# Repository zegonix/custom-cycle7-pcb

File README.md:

This repository holds the design sources for a custom PCB and plate for the cycle 7 by TKD. I ordered a prototype and got that working but I do not guarantee anything.

***Note that I used a 12 MHz oscillator instead of an 8 MHz which would be QMKs default frequency for the STM32F401. That is no problem, but requires a little extra configuration. If you don't fancy that, change the oscillator circuit to 8 MHz.***

***Also the design replaces the standard 6.25u spacebar with a 1.25u key, a 2.75u key and a 2.25u key (in this order from the left). Very few keycap sets come with a 1.25 spacebar key, so you might want to change the design to use a different spacebar configuration. If you do that you also need to adjust the plate. If you plan to use the original plate of the cycle 7 you need to change the pcb design to a default 6.25u spacebar.***

Why make my own pcb for the cycle 7? Bootloader on TKD's PCB ~~is shit~~ does not comply with my requirements. Also the firmware is proprietary.

What about this PCB? Sources are here and free to use however you want. **However use at your own risk, I do not guarantee any of this to be functional**
The QMK configuration for the keyboard is available at [zegonix/zegonix-qmk-configs/zegonix/cycle7](https://github.com/zegonix/zegonix-qmk-configs). Follow the steps described in the readme file to link the folder into your local qmk repository and build the firmware.

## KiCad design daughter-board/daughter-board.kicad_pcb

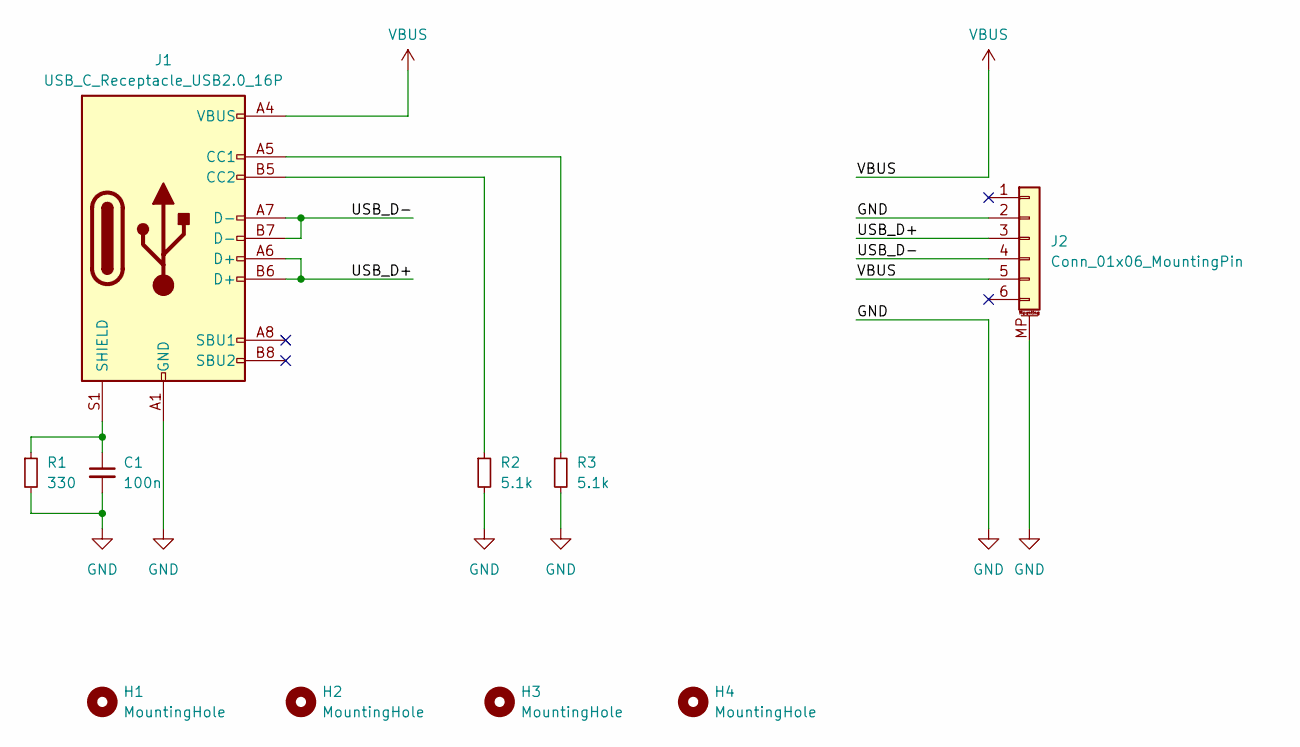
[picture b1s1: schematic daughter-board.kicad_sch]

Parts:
C1: 100n; C_0603_1608Metric
H1, H2, H3, H4: MountingHole; MountingHole_2.2mm_M2
J1: USB_C_Receptacle_USB2.0_16P; USB_C_Receptacle_HRO_TYPE-C-31-M-12
J2: Conn_01x06_MountingPin; JST_SH_SM06B-SRSS-TB_1x06-1MP_P1.00mm_Horizontal
R1: 330; R_0603_1608Metric
R2, R3: 5.1k; R_0603_1608Metric

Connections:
/USB_D+: J1.A6 (D+), J1.B6 (D+), J2.3
/USB_D-: J1.A7 (D-), J1.B7 (D-), J2.4
GND: C1.2, J1.A1 (GND), J1.A12 (GND), J1.B1 (GND), J1.B12 (GND), J2.2, J2.MP (MountPin), R1.2, R2.2, R3.2
unnamed: J1.A5 (CC1), R3.1
unnamed: J1.B5 (CC2), R2.1
unnamed: C1.1, J1.S1 (SHIELD), R1.1
VBUS: J1.A4 (VBUS), J1.A9 (VBUS), J1.B4 (VBUS), J1.B9 (VBUS), J2.5

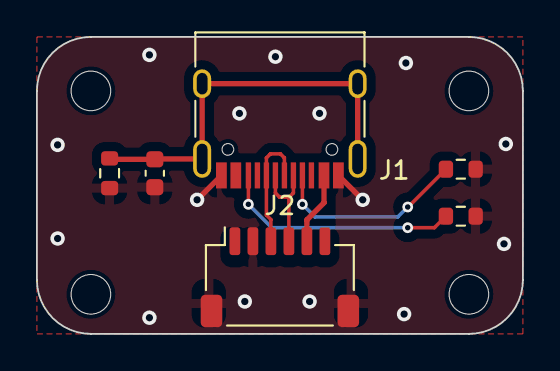
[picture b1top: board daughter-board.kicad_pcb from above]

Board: 2 copper layers, 27.0 x 16.5 mm, 10 parts (0 on the bottom side), 7 nets.

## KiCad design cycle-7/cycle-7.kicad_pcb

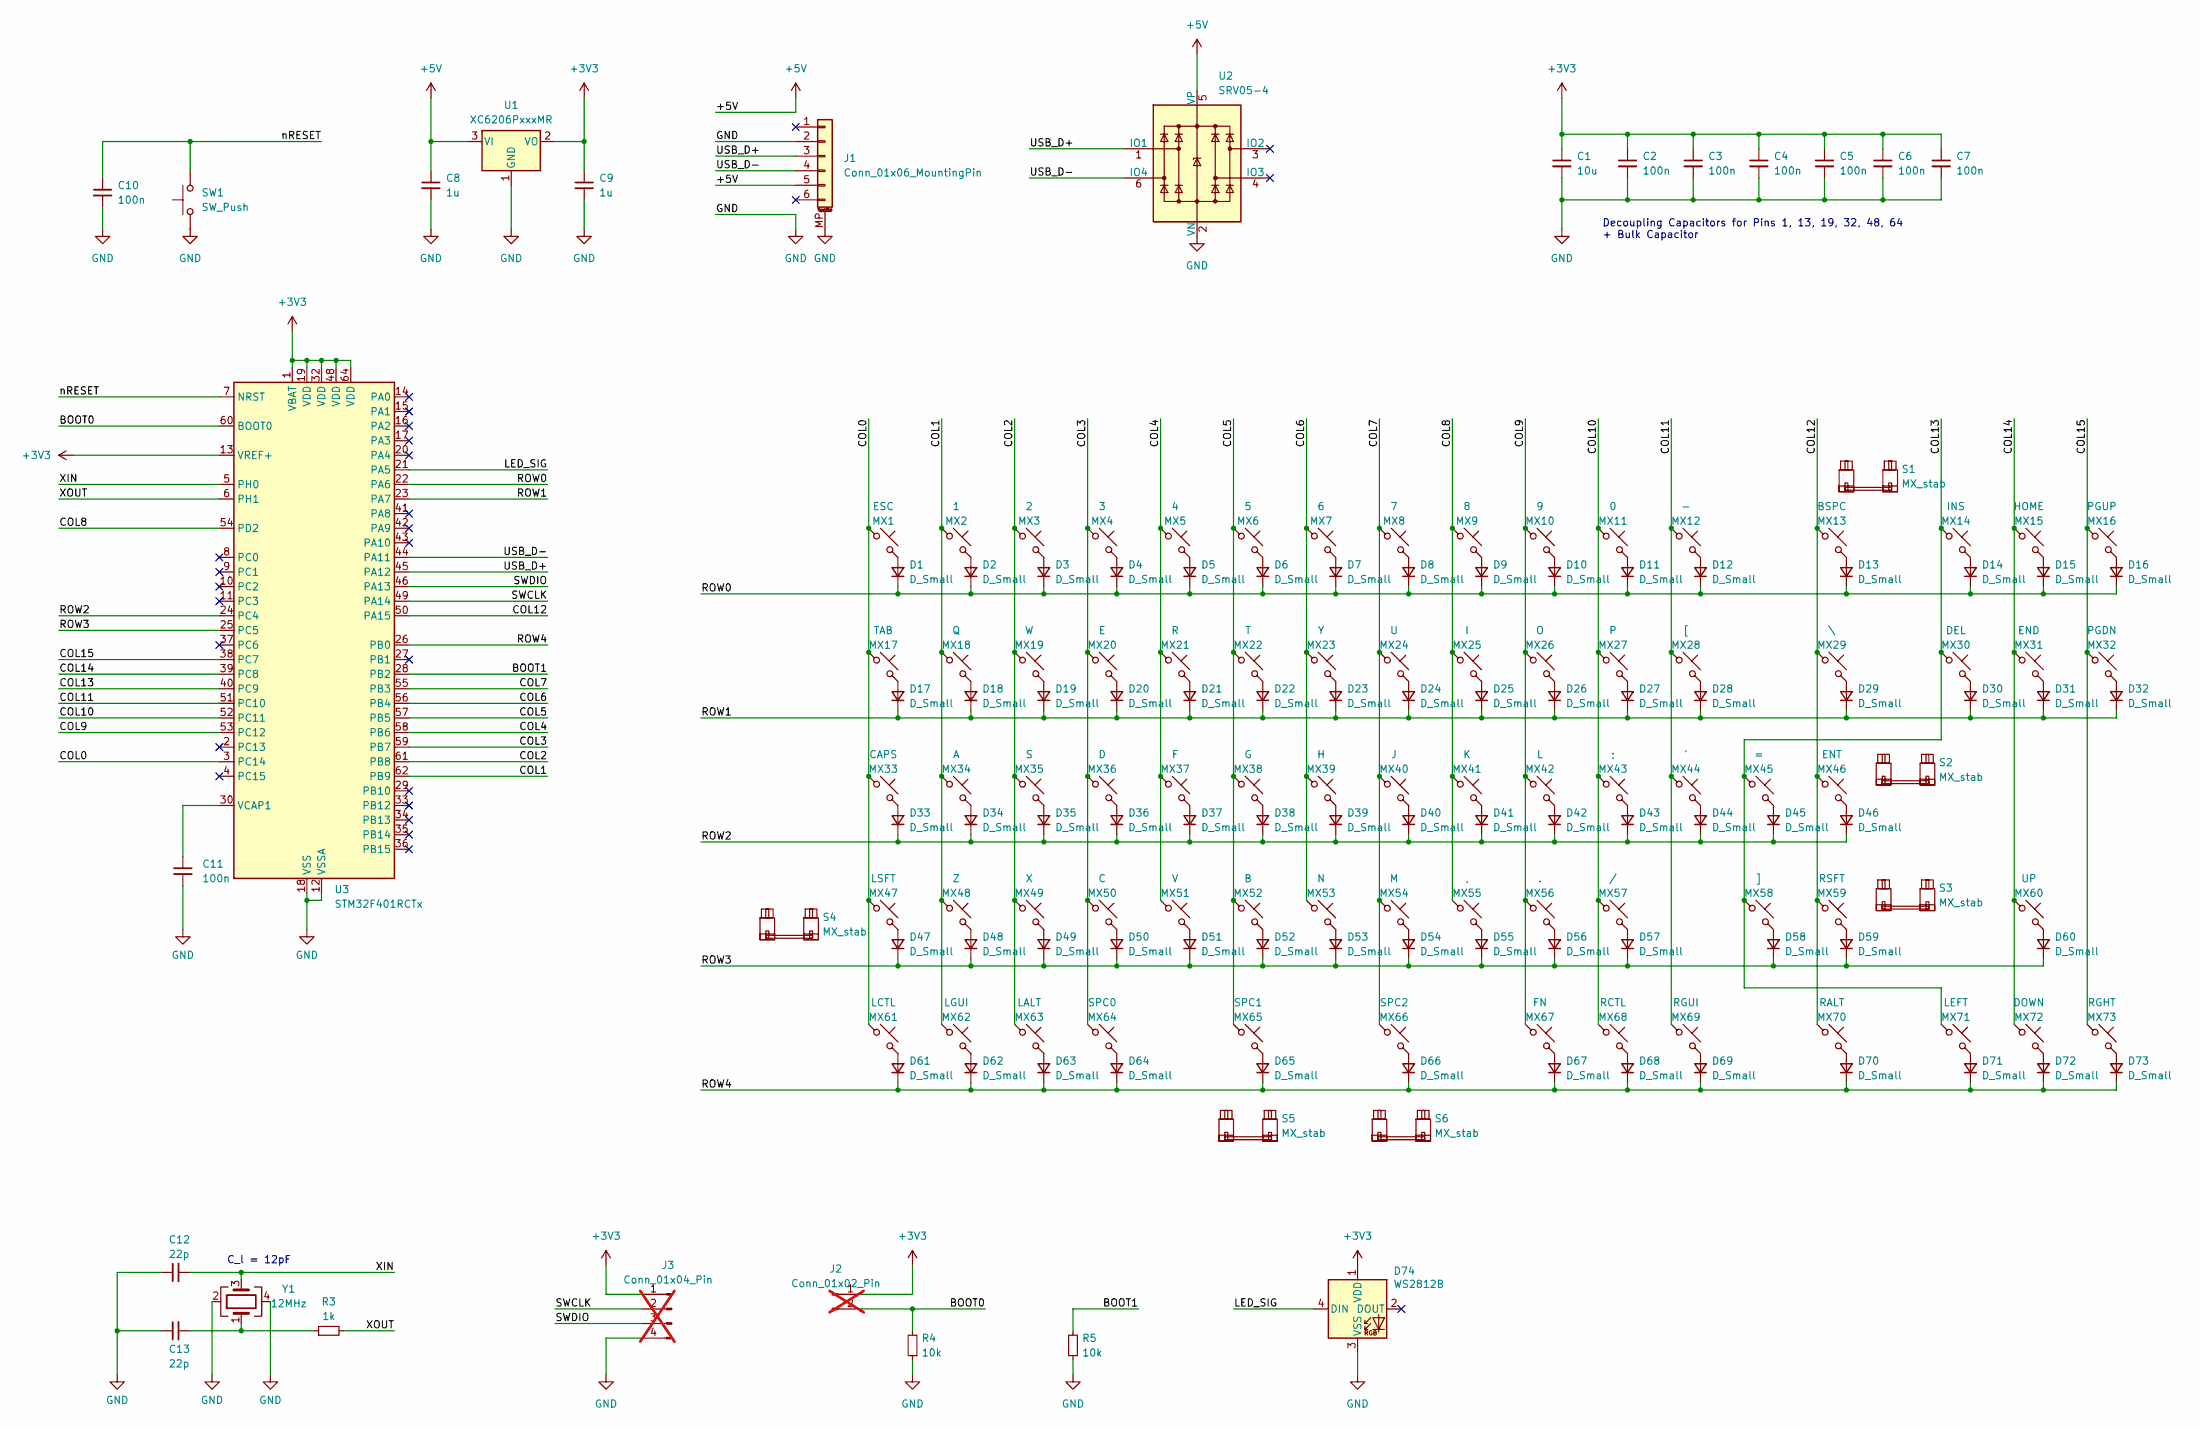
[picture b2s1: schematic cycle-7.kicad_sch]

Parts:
C1: 10u; C_0603_1608Metric
C2, C3, C4, C5, C6, C7, C10, C11: 100n; C_0603_1608Metric
C8, C9: 1u; C_0603_1608Metric
C12, C13: 22p; C_0603_1608Metric
D1, D2, D3, D4, D5, D6, D7, D8, D9, D10, D11, D12, D13, D14, D15, D16, D17, D18, D19, D20, D21, D22, D23, D24, D25, D26, D27, D28, D29, D30, D31, D32, D33, D34, D35, D36, D37, D38, D39, D40, D41, D42, D43, D44, D45, D46, D47, D48, D49, D50, D51, D52, D53, D54, D55, D56, D57, D58, D59, D60, D61, D62, D63, D64, D65, D66, D67, D68, D69, D70, D71, D72, D73: D_Small; D_SOD-123
D74: WS2812B; SK6812MINI-E_3.2x2.8_reverse_mount
J1: Conn_01x06_MountingPin; JST_SH_SM06B-SRSS-TB_1x06-1MP_P1.00mm_Horizontal
J2: Conn_01x02_Pin; PinHeader_1x02_P2.54mm_Vertical; not fitted
J3: Conn_01x04_Pin; PinHeader_1x04_P2.54mm_Vertical; not fitted
MX1, MX2, MX3, MX4, MX5, MX6, MX7, MX8, MX9, MX10, MX11, MX12, MX13, MX14, MX15, MX16, MX18, MX19, MX20, MX21, MX22, MX23, MX24, MX25, MX26, MX27, MX28, MX30, MX31, MX32, MX34, MX35, MX36, MX37, MX38, MX39, MX40, MX41, MX42, MX43, MX44, MX45, MX46, MX47, MX48, MX49, MX50, MX51, MX52, MX53, MX54, MX55, MX56, MX57, MX58, MX59, MX60, MX65, MX66, MX71, MX72, MX73: MX_SW_HS; SW_MX_HS_1u
MX17, MX29: MX_SW_HS; SW_MX_HS_1.5u
MX33: MX_SW_HS; SW_MX_HS_1.75u
MX61, MX62, MX63, MX64, MX67, MX68, MX69, MX70: MX_SW_HS; SW_MX_HS_1.25u
R3: 1k; R_0603_1608Metric
R4, R5: 10k; R_0603_1608Metric
S1: MX_stab; STAB_MX_P_2u
S2, S4, S6: MX_stab; STAB_MX_P_2.25u
S3, S5: MX_stab; STAB_MX_P_2.75u
SW1: SW_Push; SW_SPST_TL3342
U1: XC6206PxxxMR; SOT-23-3
U2: SRV05-4; SOT-23-6-routable
U3: STM32F401RCTx; LQFP-64_10x10mm_P0.5mm
Y1: 12MHz; Crystal_SMD_3225-4Pin_3.2x2.5mm

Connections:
+3V3: C1.1, C2.1, C3.1, C4.1, C5.1, C6.1, C7.1, C9.1, D74.1 (VDD), J2.1, J3.1, U1.2 (VO), U3.1 (VBAT), U3.13 (VREF+), U3.19 (VDD), U3.32 (VDD), U3.48 (VDD), U3.64 (VDD)
+5V: C8.1, J1.5, U1.3 (VI), U2.5 (VP)
/BOOT0: J2.2, R4.2, U3.60 (BOOT0)
/BOOT1: R5.2, U3.28 (PB2)
/COL0: MX1.1, MX17.1, MX33.1, MX47.1, MX61.1, U3.3 (PC14)
/COL1: MX2.1, MX18.1, MX34.1, MX48.1, MX62.1, U3.62 (PB9)
/COL2: MX3.1, MX19.1, MX35.1, MX49.1, MX63.1, U3.61 (PB8)
/COL3: MX4.1, MX20.1, MX36.1, MX50.1, MX64.1, U3.59 (PB7)
/COL4: MX5.1, MX21.1, MX37.1, MX51.1, U3.58 (PB6)
/COL5: MX6.1, MX22.1, MX38.1, MX52.1, MX65.1, U3.57 (PB5)
/COL6: MX7.1, MX23.1, MX39.1, MX53.1, U3.56 (PB4)
/COL7: MX8.1, MX24.1, MX40.1, MX54.1, MX66.1, U3.55 (PB3)
/COL8: MX9.1, MX25.1, MX41.1, MX55.1, U3.54 (PD2)
/COL9: MX10.1, MX26.1, MX42.1, MX56.1, MX67.1, U3.53 (PC12)
/COL10: MX11.1, MX27.1, MX43.1, MX57.1, MX68.1, U3.52 (PC11)
/COL11: MX12.1, MX28.1, MX44.1, MX69.1, U3.51 (PC10)
/COL12: MX13.1, MX29.1, MX46.1, MX59.1, MX70.1, U3.50 (PA15)
/COL13: MX14.1, MX30.1, MX45.1, MX58.1, MX71.1, U3.40 (PC9)
/COL14: MX15.1, MX31.1, MX60.1, MX72.1, U3.39 (PC8)
/COL15: MX16.1, MX32.1, MX73.1, U3.38 (PC7)
/LED_SIG: D74.4 (DIN), U3.21 (PA5)
/ROW0: D1.1 (K), D2.1 (K), D3.1 (K), D4.1 (K), D5.1 (K), D6.1 (K), D7.1 (K), D8.1 (K), D9.1 (K), D10.1 (K), D11.1 (K), D12.1 (K), D13.1 (K), D14.1 (K), D15.1 (K), D16.1 (K), U3.22 (PA6)
/ROW1: D17.1 (K), D18.1 (K), D19.1 (K), D20.1 (K), D21.1 (K), D22.1 (K), D23.1 (K), D24.1 (K), D25.1 (K), D26.1 (K), D27.1 (K), D28.1 (K), D29.1 (K), D30.1 (K), D31.1 (K), D32.1 (K), U3.23 (PA7)
/ROW2: D33.1 (K), D34.1 (K), D35.1 (K), D36.1 (K), D37.1 (K), D38.1 (K), D39.1 (K), D40.1 (K), D41.1 (K), D42.1 (K), D43.1 (K), D44.1 (K), D45.1 (K), D46.1 (K), U3.24 (PC4)
/ROW3: D47.1 (K), D48.1 (K), D49.1 (K), D50.1 (K), D51.1 (K), D52.1 (K), D53.1 (K), D54.1 (K), D55.1 (K), D56.1 (K), D57.1 (K), D58.1 (K), D59.1 (K), D60.1 (K), U3.25 (PC5)
/ROW4: D61.1 (K), D62.1 (K), D63.1 (K), D64.1 (K), D65.1 (K), D66.1 (K), D67.1 (K), D68.1 (K), D69.1 (K), D70.1 (K), D71.1 (K), D72.1 (K), D73.1 (K), U3.26 (PB0)
/SWCLK: J3.2, U3.49 (PA14)
/SWDIO: J3.3, U3.46 (PA13)
/USB_D+: J1.3, U2.1 (IO1), U3.45 (PA12)
/USB_D-: J1.4, U2.6 (IO4), U3.44 (PA11)
/XIN: C12.2, U3.5 (PH0), Y1.3
/XOUT: R3.2, U3.6 (PH1)
/nRESET: C10.1, SW1.2, U3.7 (NRST)
GND: C1.2, C2.2, C3.2, C4.2, C5.2, C6.2, C7.2, C8.2, C9.2, C10.2, C11.2, C12.1, C13.1, D74.3 (VSS), J1.2, J1.MP (MountPin), J3.4, R4.1, R5.1, SW1.1, U1.1 (GND), U2.2 (VN), U3.12 (VSSA), U3.18 (VSS), U3.31 (VSS), U3.47 (VSS), U3.63 (VSS), Y1.2, Y1.4
unnamed: C13.2, R3.1, Y1.1
unnamed: D1.2 (A), MX1.2
unnamed: D2.2 (A), MX2.2
unnamed: D3.2 (A), MX3.2
unnamed: D4.2 (A), MX4.2
unnamed: D5.2 (A), MX5.2
unnamed: D6.2 (A), MX6.2
unnamed: D7.2 (A), MX7.2
unnamed: D8.2 (A), MX8.2
unnamed: D9.2 (A), MX9.2
unnamed: D10.2 (A), MX10.2
unnamed: D11.2 (A), MX11.2
unnamed: D12.2 (A), MX12.2
unnamed: D13.2 (A), MX13.2
unnamed: D14.2 (A), MX14.2
unnamed: D15.2 (A), MX15.2
unnamed: D16.2 (A), MX16.2
unnamed: D17.2 (A), MX17.2
unnamed: D18.2 (A), MX18.2
unnamed: D19.2 (A), MX19.2
unnamed: D20.2 (A), MX20.2
unnamed: D21.2 (A), MX21.2
unnamed: D22.2 (A), MX22.2
unnamed: D23.2 (A), MX23.2
unnamed: D24.2 (A), MX24.2
unnamed: D25.2 (A), MX25.2
unnamed: D26.2 (A), MX26.2
unnamed: D27.2 (A), MX27.2
unnamed: D28.2 (A), MX28.2
unnamed: D29.2 (A), MX29.2
unnamed: D30.2 (A), MX30.2
unnamed: D31.2 (A), MX31.2
unnamed: D32.2 (A), MX32.2
unnamed: D33.2 (A), MX33.2
unnamed: D34.2 (A), MX34.2
unnamed: D35.2 (A), MX35.2
unnamed: D36.2 (A), MX36.2
unnamed: D37.2 (A), MX37.2
unnamed: D38.2 (A), MX38.2
unnamed: D39.2 (A), MX39.2
unnamed: D40.2 (A), MX40.2
unnamed: D41.2 (A), MX41.2
unnamed: D42.2 (A), MX42.2
unnamed: D43.2 (A), MX43.2
unnamed: D44.2 (A), MX44.2
unnamed: D45.2 (A), MX45.2
unnamed: D46.2 (A), MX46.2
unnamed: D47.2 (A), MX47.2
unnamed: D48.2 (A), MX48.2
unnamed: D49.2 (A), MX49.2
unnamed: D50.2 (A), MX50.2
unnamed: D51.2 (A), MX51.2
unnamed: D52.2 (A), MX52.2
unnamed: D53.2 (A), MX53.2
unnamed: D54.2 (A), MX54.2
unnamed: D55.2 (A), MX55.2
unnamed: D56.2 (A), MX56.2
unnamed: D57.2 (A), MX57.2
unnamed: D58.2 (A), MX58.2
unnamed: D59.2 (A), MX59.2
unnamed: D60.2 (A), MX60.2
unnamed: D61.2 (A), MX61.2
unnamed: D62.2 (A), MX62.2
unnamed: D63.2 (A), MX63.2
unnamed: D64.2 (A), MX64.2
unnamed: D65.2 (A), MX65.2
unnamed: D66.2 (A), MX66.2
unnamed: D67.2 (A), MX67.2
unnamed: D68.2 (A), MX68.2
unnamed: D69.2 (A), MX69.2
unnamed: D70.2 (A), MX70.2
unnamed: D71.2 (A), MX71.2
unnamed: D72.2 (A), MX72.2
unnamed: D73.2 (A), MX73.2
unnamed: C11.1, U3.30 (VCAP1)

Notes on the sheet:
Decoupling Capacitors for Pins 1, 13, 19, 32, 48, 64 + Bulk Capacitor
C_l = 12pF

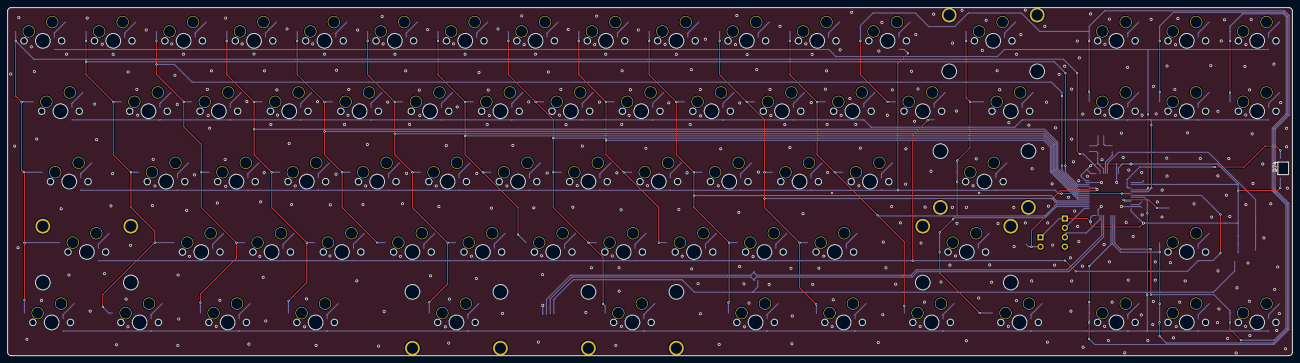
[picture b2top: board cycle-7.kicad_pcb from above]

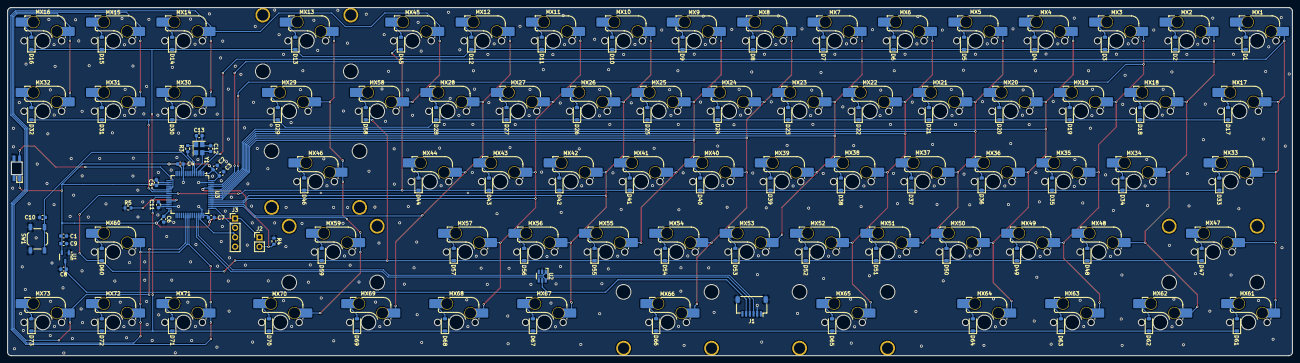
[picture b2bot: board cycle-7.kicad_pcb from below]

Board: 2 copper layers, 347.7 x 94.2 mm, 177 parts (170 on the bottom side), 109 nets.

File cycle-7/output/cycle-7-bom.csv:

"Id";"Designator";"Footprint";"Quantity";"Designation";"Supplier and ref";
1;"MX15,MX22,MX3,MX44,MX41,MX45,MX27,MX53,MX17,MX60,MX58,MX59,MX13,MX21,MX6,MX34,MX65,MX26,MX50,MX1,MX48,MX36,MX10,MX4,MX24,MX16,MX37,MX66,MX43,MX12,MX9,MX46,MX71,MX30,MX14,MX55,MX23,MX2,MX20,MX40,MX7,MX52,MX5,MX11,MX72,MX25,MX32,MX42,MX39,MX73,MX47,MX49,MX28,MX54,MX56,MX29,MX19,MX8,MX51,MX38,MX57,MX33";"SW_MX_HS_1u";62;"MX_SW_HS";;;
2;"S3,S6";"STAB_MX_P_2.75u";2;"MX_stab";;;
3;"S4,S5,S2";"STAB_MX_P_2.25u";3;"MX_stab";;;
4;"S1";"STAB_MX_P_2u";1;"MX_stab";;;
5;"D64,D17,D70,D40,D25,D59,D43,D31,D34,D45,D71,D72,D66,D29,D69,D2,D33,D68,D63,D27,D21,D44,D16,D9,D1,D47,D10,D19,D61,D24,D48,D3,D14,D37,D39,D12,D30,D53,D4,D11,D58,D73,D62,D15,D52,D42,D56,D18,D49,D32,D51,D38,D67,D22,D36,D7,D50,D35,D28,D8,D6,D57,D26,D65,D46,D23,D13,D55,D5,D54,D60,D41,D20";"D_SOD-123";73;"D_Small";;;
6;"MX18,MX31";"SW_MX_HS_1.5u";2;"MX_SW_HS";;;
7;"C11,C10,C7,C2,C4,C3,C5,C6";"C_0603_1608Metric";8;"100n";;;
8;"SW1";"SW_SPST_TL3342";1;"SW_Push";;;
9;"J2";"PinHeader_1x04_P2.54mm_Vertical";1;"Conn_01x04_Pin";;;
10;"MX67,MX68,MX64,MX61,MX69,MX63,MX62,MX70";"SW_MX_HS_1.25u";8;"MX_SW_HS";;;
11;"U3";"SOT-23-6-routable";1;"SRV05-4";;;
12;"R1,R2";"R_0603_1608Metric";2;"27";;;
13;"C9,C8";"C_0603_1608Metric";2;"1u";;;
14;"U1";"SOT-23-3";1;"XC6206PxxxMR";;;
15;"C13,C12";"C_0603_1608Metric";2;"22p";;;
16;"R3";"R_0603_1608Metric";1;"1k";;;
17;"MX35";"SW_MX_HS_1.75u";1;"MX_SW_HS";;;
18;"D74";"SK6812MINI-E_3.2x2.8_reverse_mount";1;"WS2812B";;;
19;"J1";"JST_SHL_SM06B-SHLS-TF_1x06-1MP_P1.00mm_Horizontal";1;"Conn_01x06_MountingPin";;;
20;"Y1";"Crystal_SMD_3225-4Pin_3.2x2.5mm";1;"12MHz";;;
21;"U2";"LQFP-64_10x10mm_P0.5mm";1;"STM32F401RCTx";;;
22;"C1";"C_0603_1608Metric";1;"10u";;;
23;"J3";"PinHeader_1x02_P2.54mm_Vertical";1;"Conn_01x02_Pin";;;

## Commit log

2024-04-14 fixed layout, added gnd plane stitching
2024-04-27 added a kicad project for the plate added a kicad project for the daughter board
2024-05-14 implemented newest findings from prototype and updated to kicad 8
2024-05-16 minor fixes
2024-05-24 added a readme, fixed kicad update mess..
2024-05-24 Update README.md
    .
2024-06-01 updated findings from prototype removed output folder as the vendors stock is everchanging
